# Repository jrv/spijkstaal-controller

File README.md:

# spijkstaal-controller
DC motor controller, 3-5KW / 24V

Experimental design for a replacement motor controller for a 1980's Spijkstaal electric vehicle.
This design is made in KiCad

Designed for a 24V Lead-Acid battery and a 3KW, 24V DC motor

Traditional H-bridge design with an Arduino as controlling interface.
The high power print and the controller print are seperate.

Carefull, this is work in progress. As it is now, it's sure to give you 
spectacular fireworks, but no moving vehicle!

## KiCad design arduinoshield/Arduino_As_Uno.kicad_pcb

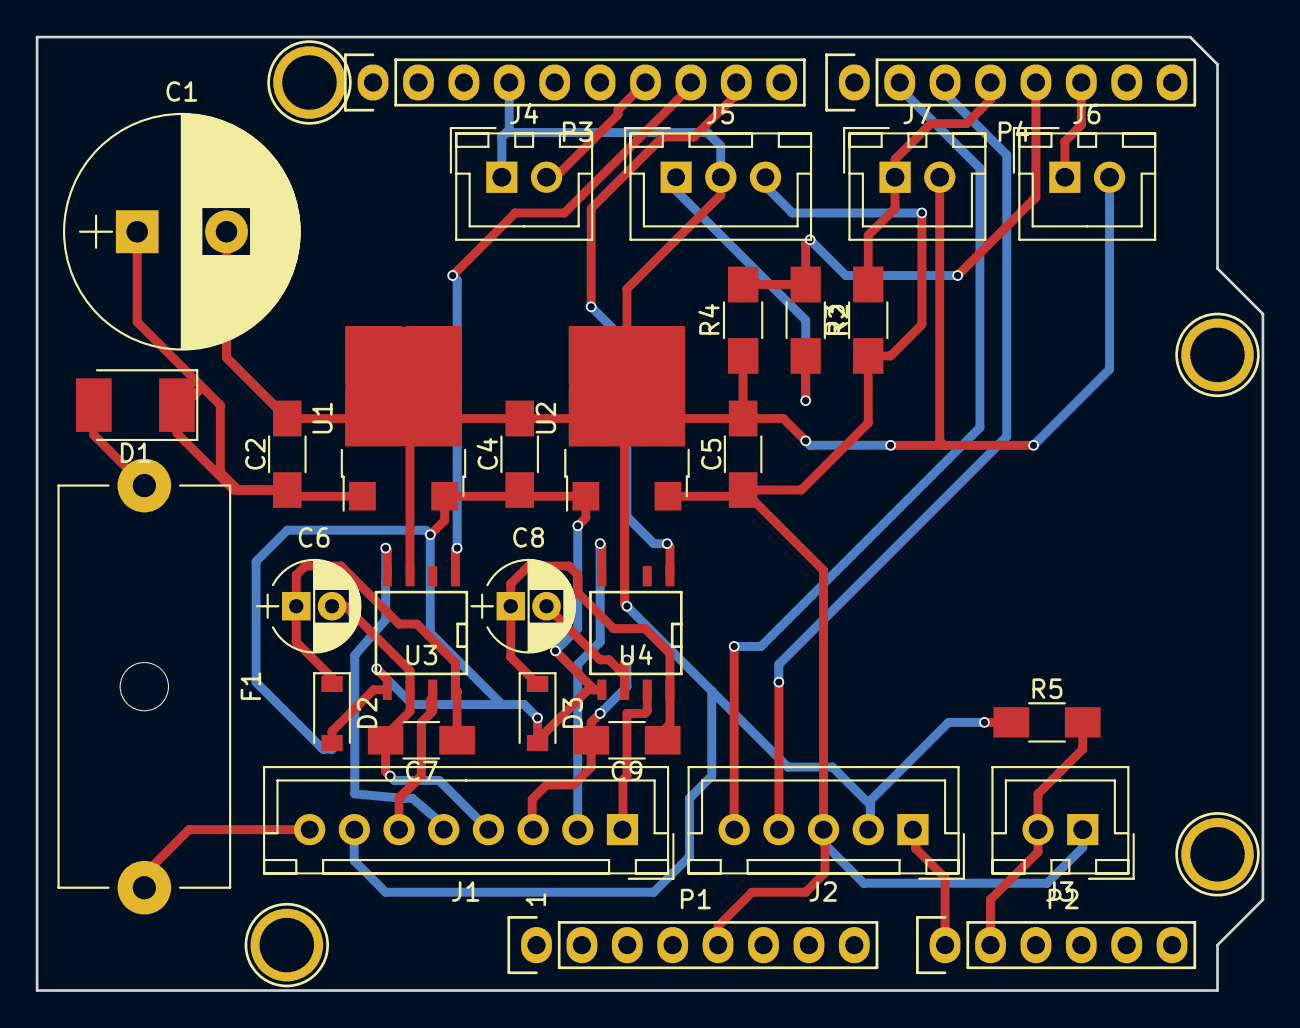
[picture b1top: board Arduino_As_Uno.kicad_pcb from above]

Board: 2 copper layers, 68.6 x 53.3 mm, 35 parts (0 on the bottom side), 25 nets.

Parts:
C1: 2200uF; CP_Radial_D13.0mm_P5.00mm
C2, C4, C5, C7, C9: 100nF; C_1206_HandSoldering
C6, C8: 4u7; CP_Radial_D5.0mm_P2.00mm
D1: MRA4007T3G; D_2114
D2, D3: 1N5819HW-7-F; D_SOD-123
F1: 1A; Fuseholder5x20_horiz_open_Schurter_0031_8201
J1: Conn_01x08; JST_XH_B08B-XH-A_08x2.50mm_Straight
J2: Conn_01x05; JST_XH_B05B-XH-A_05x2.50mm_Straight
J3, J4, J6, J7: Conn_01x02; JST_XH_B02B-XH-A_02x2.50mm_Straight
J5: Conn_01x03; JST_XH_B03B-XH-A_03x2.50mm_Straight
P1: Power; Socket_Strip_Arduino_1x08
P2: Analog; Socket_Strip_Arduino_1x06
P3: Digital; Socket_Strip_Arduino_1x10
P4: Digital; Socket_Strip_Arduino_1x08
P5, P6, P7, P8: CONN_01X01; Arduino_1pin
R2, R4, R5: 10K; R_1206_HandSoldering
R3: 4K7; R_1206_HandSoldering
U1: MC7815BD2TR4G; ATPAK-2
U2: L7805CD2T-TR; ATPAK-2
U3, U4: IR2184SPBF; SOIC-8-N

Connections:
+5V: C5.1, J2.3, J3.1, J5.3, P1.5, R3.1, U2.3
/2: J6.1, P4.6
/3(**): P4.5, R2.1, R4.2
/4: J7.1, P4.4, R3.2
/5(**): J2.4, P4.3
/6(**): J2.5, P4.2
/9(**): P3.9, U4.1
/10(**/SS): P3.8, U3.1
/11(**/MOSI): J4.2, P3.7
/24V-Fused: D1.2, F1.1
/+15V: C4.1, D2.2, D3.2, U1.3, U2.1, U3.5, U4.5
/A0: J2.1, P2.1
/A1: J3.2, P2.2, R5.2
GND: C1.2, C2.2, C4.2, C5.2, J1.7, J2.2, J4.1, J5.2, J6.2, J7.2, P1.6, P1.7, P3.4, R4.1, R5.1, U1.2, U2.2, U3.3, U4.3
unnamed: C1.1, C2.1, D1.1, U1.1
unnamed: C6.1, C7.1, D2.1, U3.8
unnamed: C6.2, C7.2, J1.4, U3.6
unnamed: C8.1, C9.1, D3.1, U4.8
unnamed: C8.2, C9.2, J1.3, U4.6
unnamed: F1.2, J1.8
unnamed: J1.1, U4.7
unnamed: J1.2, U4.4
unnamed: J1.5, U3.4
unnamed: J1.6, U3.7
unnamed: J5.1, R2.2

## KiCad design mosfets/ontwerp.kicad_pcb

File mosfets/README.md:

The design in this directory has been replaced by the one in directory
"controller"

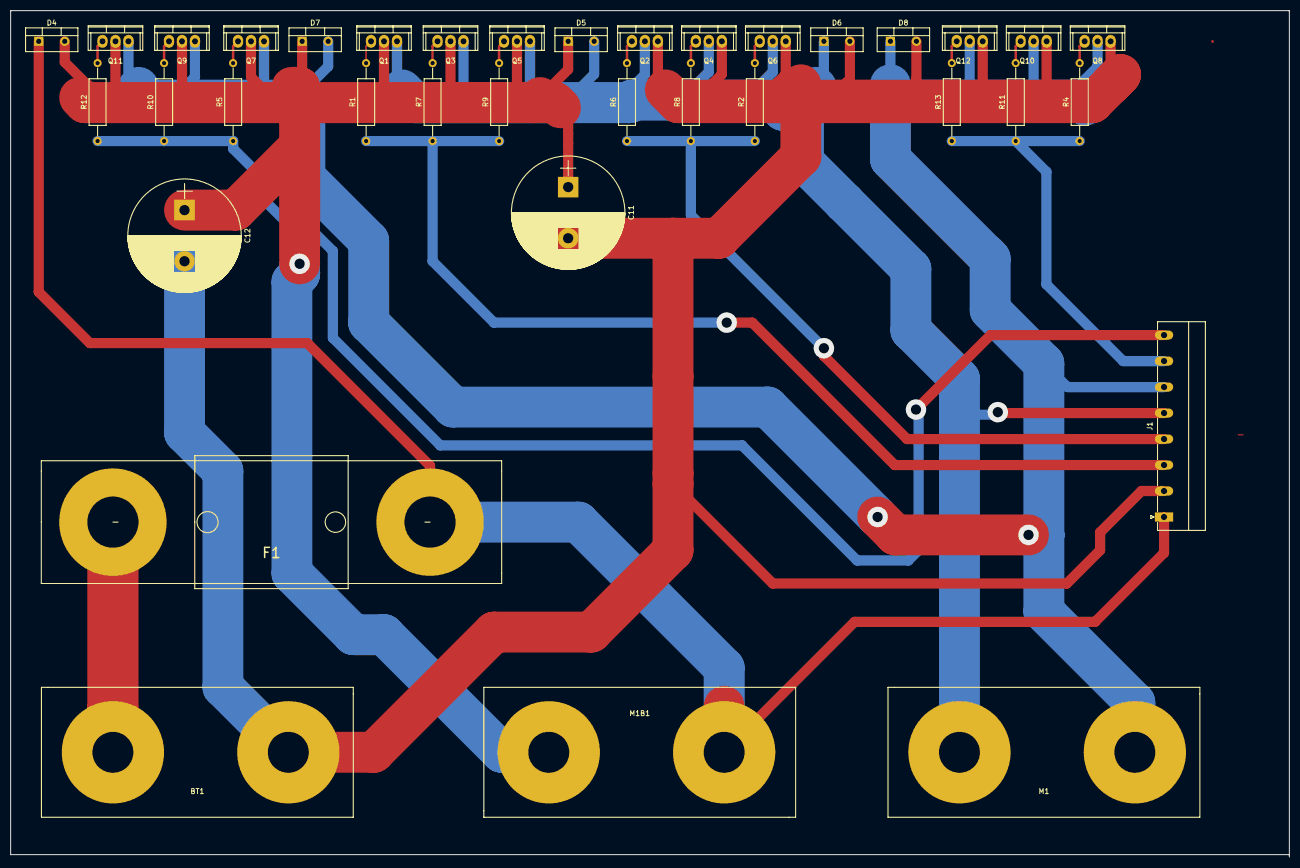
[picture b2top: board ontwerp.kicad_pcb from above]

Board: 2 copper layers, 250.0 x 165.5 mm, 36 parts (0 on the bottom side), 22 nets.

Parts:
BT1: 24V Battery; AccuDraad
C11, C12: 2000uF; CP_Radial_D22.0mm_P10.00mm_SnapIn
D4, D5, D6, D7, D8: D; TO-220-2_Vertical
F1: 300A (slow); BoltDownFuse
J1: Conn_01x08; PhoenixContact_MC-G_08x5.08mm_Angled
M1, M1B1: MOTOR; AccuDraad
Q1, Q2, Q3, Q4, Q5, Q6, Q7, Q8, Q9, Q10, Q11, Q12: PSMN3R4; TO-220
R1, R2, R4, R5, R6, R7, R8, R9, R10, R11, R12, R13: 4R7; R_Axial_DIN0309_L9.0mm_D3.2mm_P15.24mm_Horizontal

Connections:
/+24V: D4.1, F1.2, J1.1, M1B1.1
/+24V-NF: BT1.1, F1.1
/GND: BT1.2, C11.2, C12.2, D6.2, D8.2, J1.2, Q2.3, Q4.3, Q6.3, Q8.3, Q10.3, Q12.3
/M1: D5.2, D6.1, J1.5, M1.1, Q1.3, Q2.2, Q3.3, Q4.2, Q5.3, Q6.2
/M2: D7.2, D8.1, J1.6, M1.2, Q7.3, Q8.2, Q9.3, Q10.2, Q11.3, Q12.2
/M-IN: C11.1, C12.1, D4.2, D5.1, D7.1, M1B1.2, Q1.2, Q3.2, Q5.2, Q7.2, Q9.2, Q11.2
/SIG1H: J1.3, R1.1, R7.1, R9.1
/SIG1L: J1.4, R2.1, R6.1, R8.1
/SIG2H: J1.8, R5.1, R10.1, R12.1
/SIG2L: J1.7, R4.1, R11.1, R13.1
unnamed: Q1.1, R1.2
unnamed: Q2.1, R6.2
unnamed: Q3.1, R7.2
unnamed: Q4.1, R8.2
unnamed: Q5.1, R9.2
unnamed: Q6.1, R2.2
unnamed: Q7.1, R5.2
unnamed: Q8.1, R4.2
unnamed: Q9.1, R10.2
unnamed: Q10.1, R11.2
unnamed: Q11.1, R12.2
unnamed: Q12.1, R13.2

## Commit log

2017-10-16 Added mosfet design
2017-10-16 Added arduino shield v1
2017-10-16 Casing Mosfet part
2017-10-16 Cooler block for Mosfets & Diodes
2017-10-16 bill of materials
2017-10-18 redesigned arduino shield for with connectors and smd parts
2017-11-24 New controller design
